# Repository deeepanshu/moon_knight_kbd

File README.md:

# Moon Knight Keyboard

A custom split keyboard project with multiple hardware iterations and utilities.

## Project Structure

- **moon_knight_v1/** - Initial keyboard design
- **moon_knight_v2_left/** & **moon_knight_v2_right/** - Second iteration split keyboard
- **moon_knight_v3/** - Third iteration
- **moon_knight_v4/** - Latest iteration
- **firmwares/** - Keyboard firmware configurations
- **keeb_utils/** - Utility tools for the keyboard
  - **layer-display/** - Real-time layer visualization utility

## Resources

- [Switch Placement Grid Guide](https://discord.com/channels/1025609366180728904/1096999853084655717/1358123429684838441) - Discord discussion on proper switch placement in grid layout

## Hardware Files

- `moon_knight_v2_case_design.stl` - Case design for v2
- `moon_knight_v2_switch_plates.stl` - Switch plates for v2

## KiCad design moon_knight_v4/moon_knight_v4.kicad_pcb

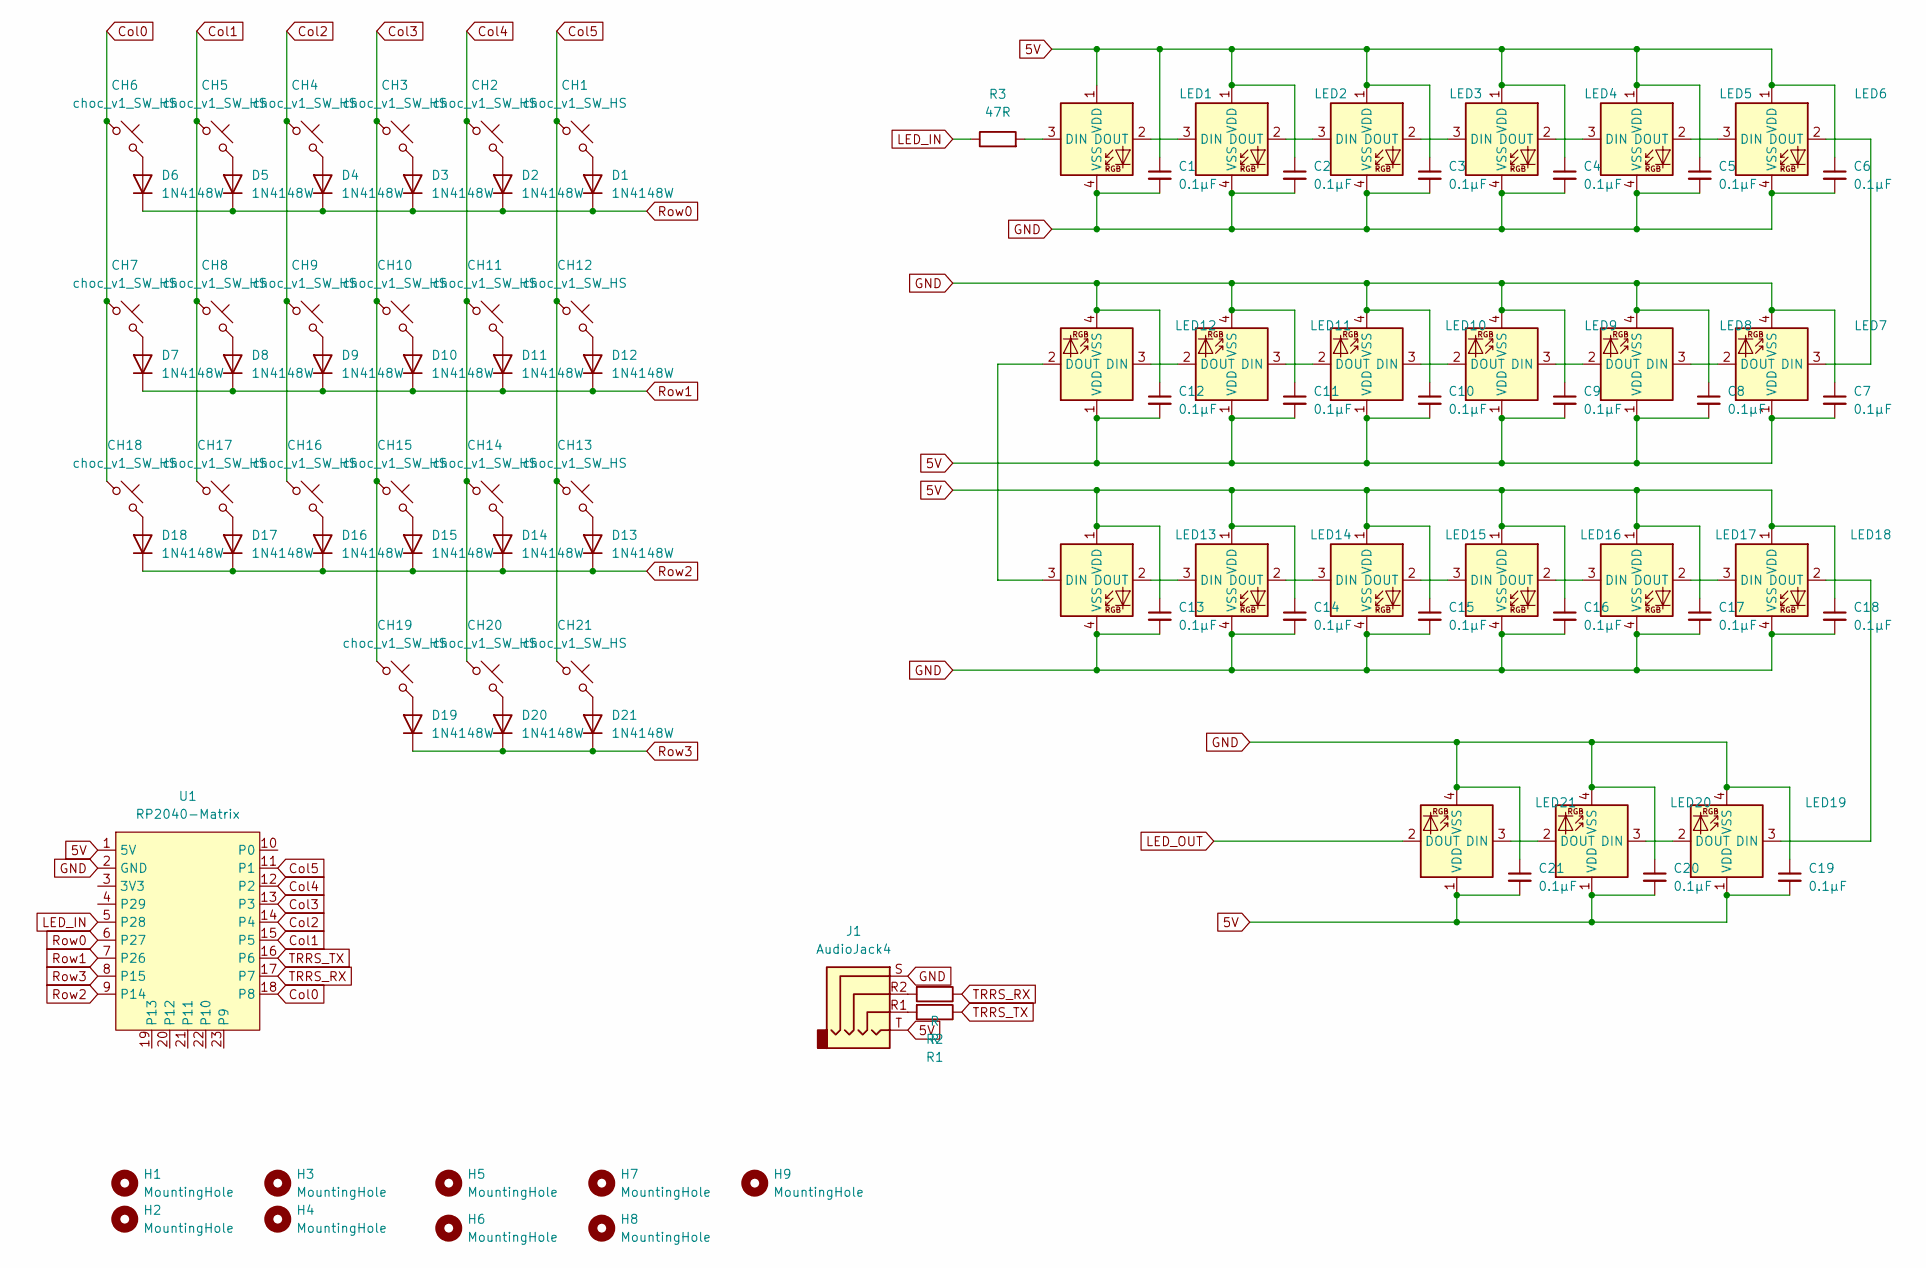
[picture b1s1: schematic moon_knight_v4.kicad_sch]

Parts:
C1, C2, C3, C4, C5, C6, C7, C8, C9, C10, C11, C12, C13, C14, C15, C16, C17, C18, C19, C20, C21: 0.1µF; C_1206_3216Metric
CH1, CH2, CH3, CH4, CH5, CH6, CH7, CH8, CH9, CH10, CH11, CH12, CH13, CH14, CH15, CH16, CH17, CH18, CH19, CH20: choc_v1_SW_HS; SW_choc_v1_HS_CPG135001S30_1u
CH21: choc_v1_SW_HS; SW_choc_v1_HS_CPG135001S30_1.5u
D1, D2, D3, D4, D5, D6, D7, D8, D9, D10, D11, D12, D13, D14, D15, D16, D17, D18, D19, D20, D21: 1N4148W; D_SOD-123
H1, H2, H3, H4, H5, H6, H7, H8, H9: MountingHole; MountingHole_2.2mm_M2
J1: AudioJack4; CON_MJ-4PP-9
LED1, LED2, LED3, LED4, LED5, LED6, LED7, LED8, LED9, LED10, LED11, LED12, LED13, LED14, LED15, LED16, LED17, LED18, LED19, LED20, LED21: SK6812MINI-E; LED_6028R
R1, R2: R; R_1206_3216Metric_Pad1.30x1.75mm_HandSolder
R3: 47R; R_1206_3216Metric_Pad1.30x1.75mm_HandSolder
U1: RP2040-Matrix; RP2040-Matrix_AH

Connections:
5V: C1.1, C2.1, C3.1, C4.1, C5.1, C6.1, C7.2, C8.2, C9.2, C10.2, C11.2, C12.2, C13.1, C14.1, C15.1, C16.1, C17.1, C18.1, C19.2, C20.2, C21.2, J1.T, LED1.1 (VDD), LED2.1 (VDD), LED3.1 (VDD), LED4.1 (VDD), LED5.1 (VDD), LED6.1 (VDD), LED7.1 (VDD), LED8.1 (VDD), LED9.1 (VDD), LED10.1 (VDD), LED11.1 (VDD), LED12.1 (VDD), LED13.1 (VDD), LED14.1 (VDD), LED15.1 (VDD), LED16.1 (VDD), LED17.1 (VDD), LED18.1 (VDD), LED19.1 (VDD), LED20.1 (VDD), LED21.1 (VDD), U1.1 (5V)
Col0: CH6.1, CH7.1, CH18.1, U1.18 (P8)
Col1: CH5.1, CH8.1, CH17.1, U1.15 (P5)
Col2: CH4.1, CH9.1, CH16.1, U1.14 (P4)
Col3: CH3.1, CH10.1, CH15.1, CH19.1, U1.13 (P3)
Col4: CH2.1, CH11.1, CH14.1, CH20.1, U1.12 (P2)
Col5: CH1.1, CH12.1, CH13.1, CH21.1, U1.11 (P1)
GND: C1.2, C2.2, C3.2, C4.2, C5.2, C6.2, C7.1, C8.1, C9.1, C10.1, C11.1, C12.1, C13.2, C14.2, C15.2, C16.2, C17.2, C18.2, C19.1, C20.1, C21.1, J1.S, LED1.4 (VSS), LED2.4 (VSS), LED3.4 (VSS), LED4.4 (VSS), LED5.4 (VSS), LED6.4 (VSS), LED7.4 (VSS), LED8.4 (VSS), LED9.4 (VSS), LED10.4 (VSS), LED11.4 (VSS), LED12.4 (VSS), LED13.4 (VSS), LED14.4 (VSS), LED15.4 (VSS), LED16.4 (VSS), LED17.4 (VSS), LED18.4 (VSS), LED19.4 (VSS), LED20.4 (VSS), LED21.4 (VSS), U1.2 (GND)
LED_IN: R3.1, U1.5 (P28)
LED_OUT: LED21.2 (DOUT)
unnamed: CH1.2, D1.2 (A)
unnamed: CH2.2, D2.2 (A)
unnamed: CH3.2, D3.2 (A)
unnamed: CH4.2, D4.2 (A)
unnamed: CH5.2, D5.2 (A)
unnamed: CH6.2, D6.2 (A)
unnamed: CH7.2, D7.2 (A)
unnamed: CH8.2, D8.2 (A)
unnamed: CH9.2, D9.2 (A)
unnamed: CH10.2, D10.2 (A)
unnamed: CH11.2, D11.2 (A)
unnamed: CH12.2, D12.2 (A)
unnamed: CH13.2, D13.2 (A)
unnamed: CH14.2, D14.2 (A)
unnamed: CH15.2, D15.2 (A)
unnamed: CH16.2, D16.2 (A)
unnamed: CH17.2, D17.2 (A)
unnamed: CH18.2, D18.2 (A)
unnamed: CH19.2, D19.2 (A)
unnamed: CH20.2, D20.2 (A)
unnamed: CH21.2, D21.2 (A)
unnamed: J1.R1, R1.2
unnamed: J1.R2, R2.2
unnamed: LED1.3 (DIN), R3.2
unnamed: LED1.2 (DOUT), LED2.3 (DIN)
unnamed: LED2.2 (DOUT), LED3.3 (DIN)
unnamed: LED3.2 (DOUT), LED4.3 (DIN)
unnamed: LED4.2 (DOUT), LED5.3 (DIN)
unnamed: LED5.2 (DOUT), LED6.3 (DIN)
unnamed: LED6.2 (DOUT), LED7.3 (DIN)
unnamed: LED7.2 (DOUT), LED8.3 (DIN)
unnamed: LED8.2 (DOUT), LED9.3 (DIN)
unnamed: LED9.2 (DOUT), LED10.3 (DIN)
unnamed: LED10.2 (DOUT), LED11.3 (DIN)
unnamed: LED11.2 (DOUT), LED12.3 (DIN)
unnamed: LED12.2 (DOUT), LED13.3 (DIN)
unnamed: LED13.2 (DOUT), LED14.3 (DIN)
unnamed: LED14.2 (DOUT), LED15.3 (DIN)
unnamed: LED15.2 (DOUT), LED16.3 (DIN)
unnamed: LED16.2 (DOUT), LED17.3 (DIN)
unnamed: LED17.2 (DOUT), LED18.3 (DIN)
unnamed: LED18.2 (DOUT), LED19.3 (DIN)
unnamed: LED19.2 (DOUT), LED20.3 (DIN)
unnamed: LED20.2 (DOUT), LED21.3 (DIN)
Row0: D1.1 (K), D2.1 (K), D3.1 (K), D4.1 (K), D5.1 (K), D6.1 (K), U1.6 (P27)
Row1: D7.1 (K), D8.1 (K), D9.1 (K), D10.1 (K), D11.1 (K), D12.1 (K), U1.7 (P26)
Row2: D13.1 (K), D14.1 (K), D15.1 (K), D16.1 (K), D17.1 (K), D18.1 (K), U1.9 (P14)
Row3: D19.1 (K), D20.1 (K), D21.1 (K), U1.8 (P15)
TRRS_RX: R2.1, U1.17 (P7)
TRRS_TX: R1.1, U1.16 (P6)

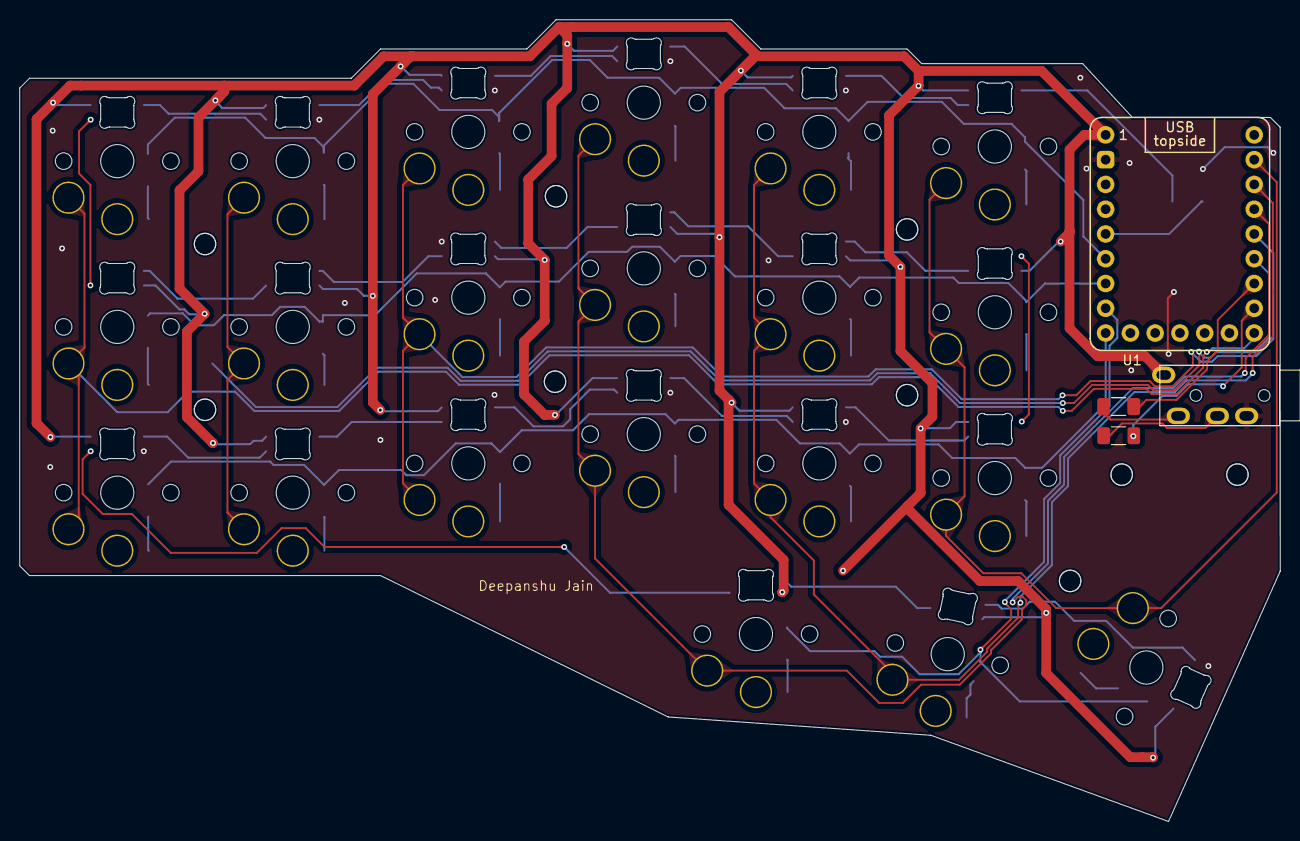
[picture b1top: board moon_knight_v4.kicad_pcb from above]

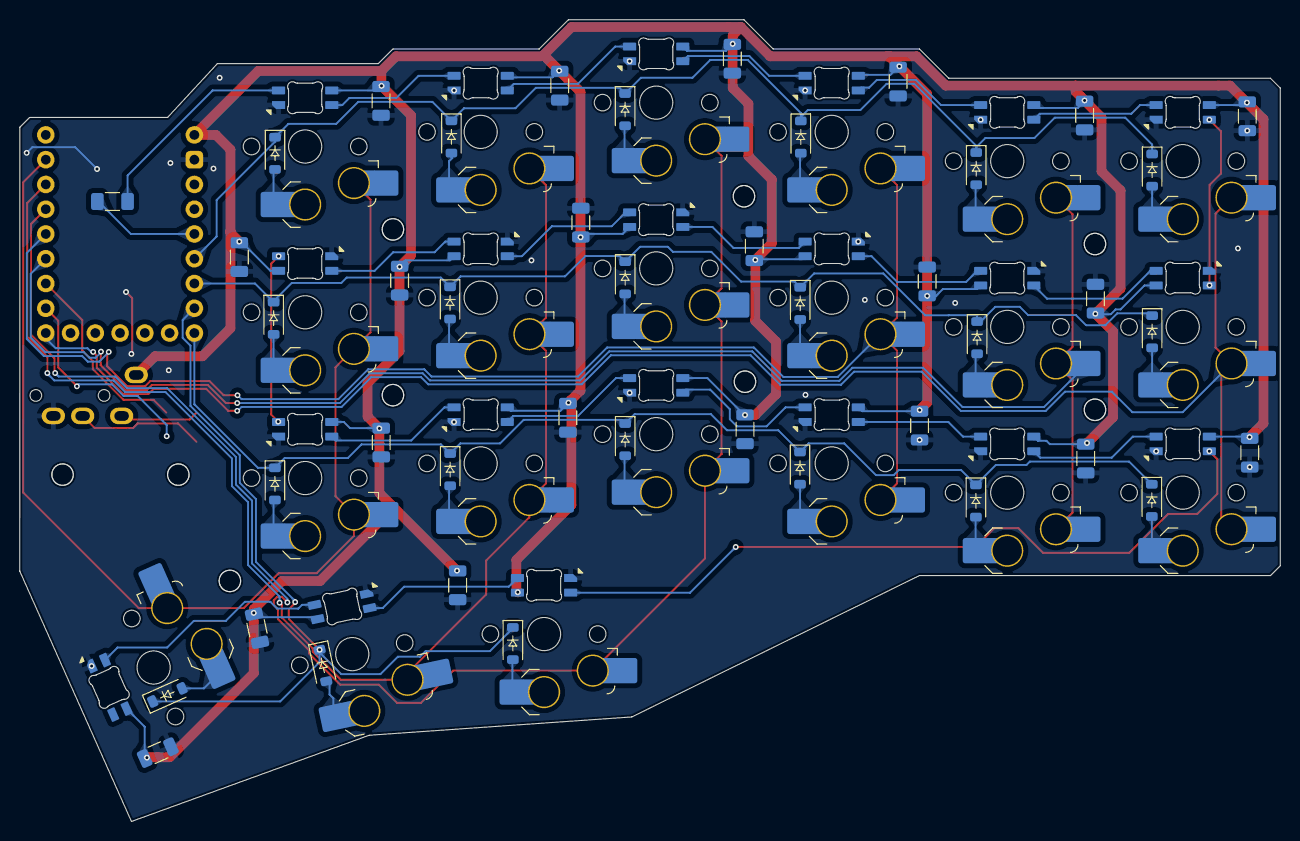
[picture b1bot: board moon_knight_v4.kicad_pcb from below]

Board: 2 copper layers, 129.3 x 82.2 mm, 98 parts (85 on the bottom side), 59 nets.

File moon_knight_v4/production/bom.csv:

Designator,Footprint,Quantity,Value,LCSC Part #
"C1, C10, C11, C12, C13, C14, C15, C16, C17, C18, C19, C2, C20, C21, C3, C4, C5, C6, C7, C8, C9",1206,21,0.1µF,
"CH1, CH10, CH11, CH12, CH13, CH14, CH15, CH16, CH17, CH18, CH19, CH2, CH20, CH3, CH4, CH5, CH6, CH7, CH8, CH9",SW_choc_v1_HS_CPG135001S30_1u,20,choc_v1_SW_HS,
CH21,SW_choc_v1_HS_CPG135001S30_1.5u,1,choc_v1_SW_HS,
"D1, D10, D11, D12, D13, D14, D15, D16, D17, D18, D19, D2, D20, D21, D3, D4, D5, D6, D7, D8, D9",D_SOD-123,21,1N4148W,
J1,CON_MJ-4PP-9,1,AudioJack4,
J2,OLED-128x32,1,OLED_128x32,
"LED1, LED10, LED11, LED12, LED13, LED14, LED15, LED16, LED17, LED18, LED19, LED2, LED20, LED21, LED3, LED4, LED5, LED6, LED7, LED8, LED9",LED_6028R,21,SK6812MINI-E,
"R1, R2",1206,2,R,
R3,1206,1,47R,
SW1,SW_SPST_TS-1088-xR020,1,SW_PUSH,
U1,Sea-Picro_EXT_Module_Flipped,1,Sea-Picro,

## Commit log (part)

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2025-11-12 init
2025-11-12 Add splits
2025-11-22 Final
2025-11-26 Fixes
2025-11-26 setup vial
2025-11-27 something
2025-12-06 Add readme
2025-12-09 Update config
2025-12-19 Update keymaps
2025-12-30 V4 keyboard
2026-01-15 v4 keeb
2026-01-15 some commits
2026-01-31 Shadow Knight firmware
